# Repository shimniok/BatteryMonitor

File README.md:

# BatteryMonitor
Automotive battery and alternator monitor

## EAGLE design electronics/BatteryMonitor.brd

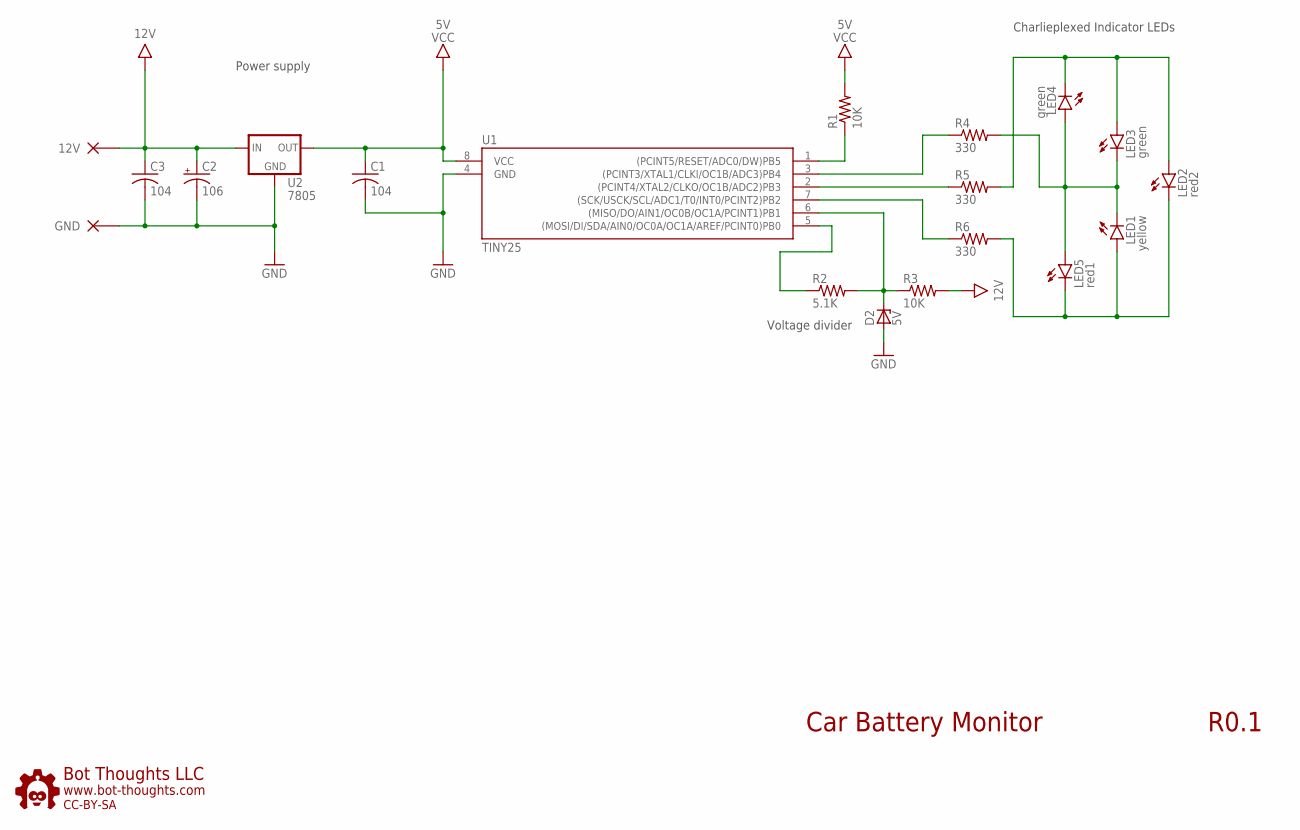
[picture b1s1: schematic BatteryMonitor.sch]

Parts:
C1: 104; C050-024X044
C2: 106; E2,5-6
C3: 104; C025-024X044
D2: 5V; DO35Z7
LED1: yellow; LED5MMRA
LED2: red2; LED5MMRA
LED3, LED4: green; LED5MMRA
LED5: red1; LED5MMRA
R1, R3: 10K; 0204/5
R2: 5.1K; 0204/5
R4, R5, R6: 330; 0204/5
U1: TINY25; DIL08
U2: 7805; TO220BH-NH
U$5: BTLOGO-LOGO-MD; BTLOGOM
X1: 12V; PAD_18GA
X2: GND; PAD_18GA

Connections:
12V: C2.+, C3.1 (+), R3.2, U2.1 (IN), X1.P$1
GND: C1.2 (-), C2.-, C3.2 (-), D2.A, U1.4 (GND), U2.2 (GND), X2.P$1
unnamed: R1.1, U1.1 ((PCINT5/RESET/ADC0/DW)PB5)
unnamed: LED2.A, LED3.A, LED4.C, R5.2
unnamed: LED1.C, LED3.C, LED4.A, LED5.A, R4.2
unnamed: R4.1, U1.3 ((PCINT3/XTAL1/CLKI/OC1B/ADC3)PB4)
unnamed: LED1.A, LED2.C, LED5.C, R6.2
unnamed: R5.1, U1.2 ((PCINT4/XTAL2/CLKO/OC1B/ADC2)PB3)
unnamed: R6.1, U1.7 ((SCK/USCK/SCL/ADC1/T0/INT0/PCINT2)PB2)
unnamed: R2.1, U1.5 ((MOSI/DI/SDA/AIN0/OC0A/OC1A/AREF/PCINT0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)
VCC: C1.1 (+), R1.2, U1.8 (VCC), U2.3 (OUT)
VTEST: D2.C, R2.2, R3.1, U1.6 ((MISO/DO/AIN1/OC0B/OC1A/PCINT1)PB1)

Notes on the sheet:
Car Battery Monitor
R0.1
Charlieplexed Indicator LEDs
Voltage divider
Power supply

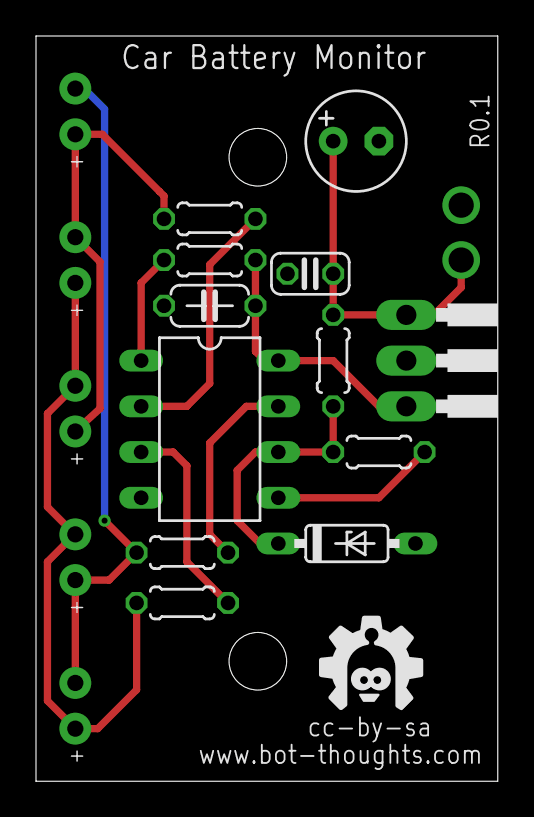
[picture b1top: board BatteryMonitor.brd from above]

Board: 2 copper layers, 25.7 x 41.4 mm, 20 parts (0 on the bottom side), 12 nets.

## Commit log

2017-03-14 Initial design version
2017-03-14 Added calculation spreadsheet
2017-03-14 created electronics & firmware subdirectories and moved eagle files
2017-03-14 updated cal to compute voltage divider current and voltage and ADC value

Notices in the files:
electronics/BatteryMonitor.brd:
cc-by-sa
